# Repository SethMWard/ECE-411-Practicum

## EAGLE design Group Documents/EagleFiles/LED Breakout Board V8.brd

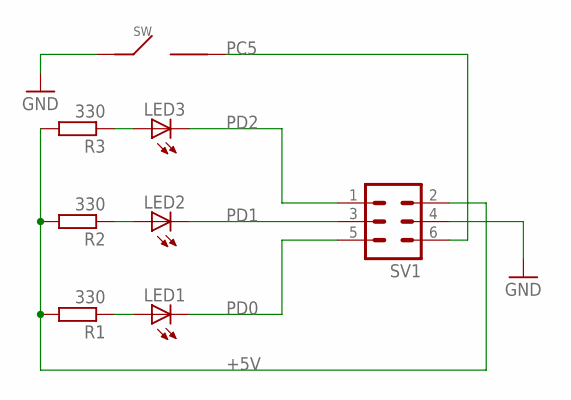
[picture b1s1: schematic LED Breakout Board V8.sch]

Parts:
LED1, LED2, LED3: LED10MM
R1, R2, R3: 330; 0207/10
SV1: MA03-2
SW: PUSHBUTTON

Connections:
+5V: R1.2, R2.2, R3.2, SV1.2
GND: SV1.4, SW.IN
unnamed: LED3.A, R3.1
unnamed: LED2.A, R2.1
unnamed: LED1.A, R1.1
PC5: SV1.6, SW.OUT
PD0: LED1.K (C), SV1.5
PD1: LED2.K (C), SV1.3
PD2: LED3.K (C), SV1.1

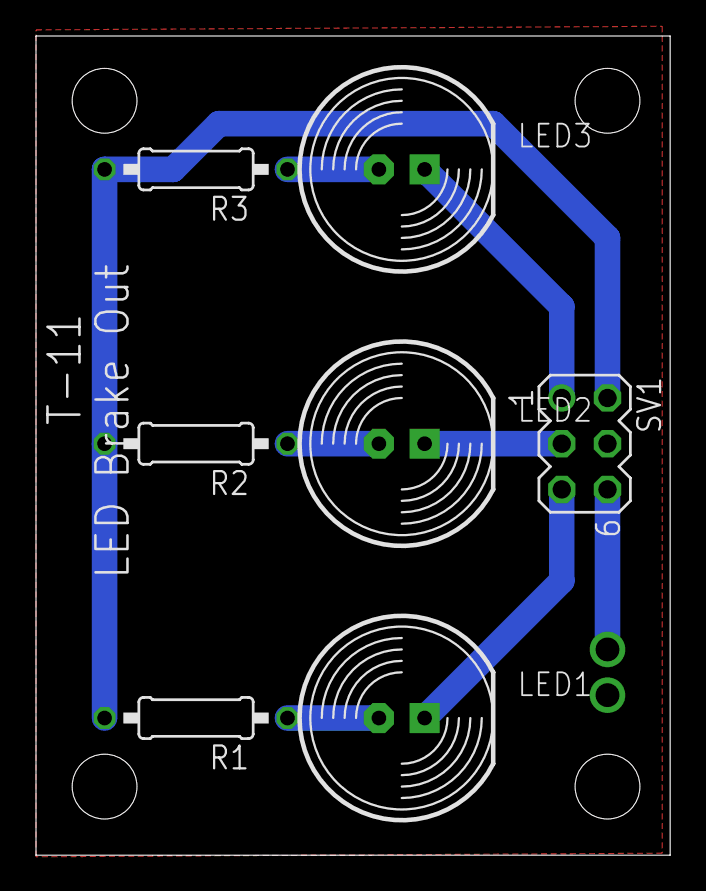
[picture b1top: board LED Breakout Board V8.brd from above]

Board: 2 copper layers, 35.2 x 45.5 mm, 8 parts (0 on the bottom side), 9 nets.

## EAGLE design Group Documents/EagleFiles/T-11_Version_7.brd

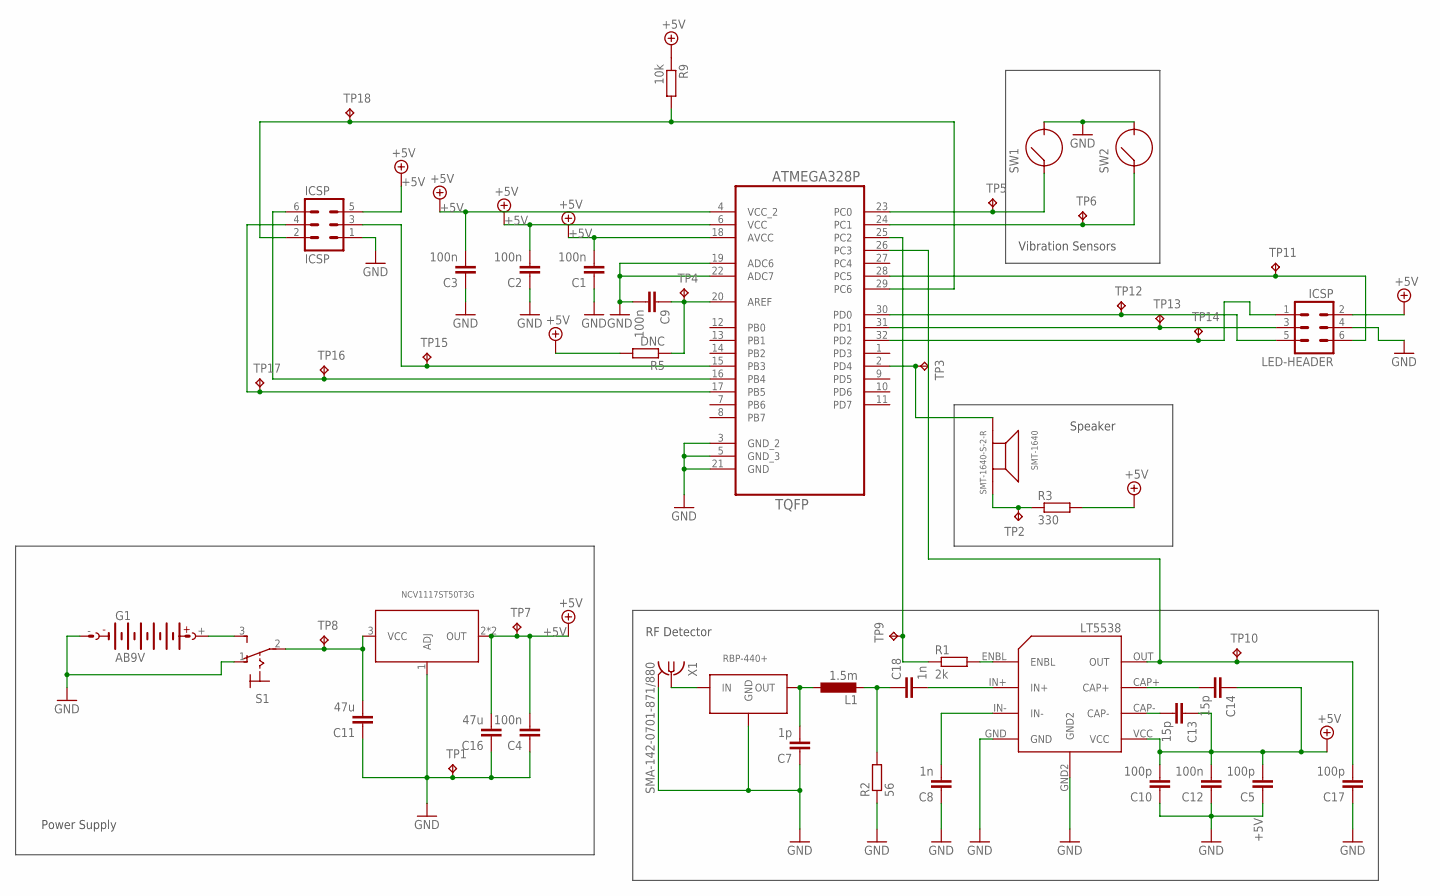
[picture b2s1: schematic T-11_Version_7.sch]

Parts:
C1, C2, C3, C4, C9, C12: 100n; C0805
C5, C10, C17: 100p; C0805
C7: 1p; C0805
C8, C18: 1n; C0805
C11, C16: 47u; C0805
C13, C14: 15p; C0805
G1: AB9V
ICSP: ICSP; MA03-2
L1: 1.5m; L2825P
LED-HEADER: ICSP; MA03-2
LT5538: LT5538
NVC1: NCV1117ST50T3G; SOT223
R1: 2k; R0805
R2: 56; R0805
R3: 330; R0805
R5: DNC; R0805
R9: 10k; R0805
RBP-440+: RBP-440+; GP731
S1: 320-916
SMT-1640: SMT-1640-S-2-R; SMT-1640
SW1, SW2: SW-1801X
TP1, TP2, TP3, TP4, TP5, TP6, TP7, TP8, TP9, TP10, TP11, TP12, TP13, TP14, TP15, TP16, TP17, TP18: TPTP10R; TP10R
U1: ATMEGA328P-AU; QFP80P900X900X120-32N
X1: SMA-142-0701-871/880; SMA-142-0701-871

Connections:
+5V: C1.2, C2.2, C3.2, C4.2, C5.2, C10.2, C12.2, C13.1, C14.1, C16.2, ICSP.5, LED-HEADER.2, LT5538.VCC, NVC1.2 (OUT), NVC1.4 (OUT), R3.2, R5.2, R9.1, TP7.TP, U1.4 (VCC_2), U1.6 (VCC), U1.18 (AVCC)
ANT_IN_1: C7.2, L1.1, RBP-440+.6 (OUT)
ANT_IN_2: C18.1, L1.2, R2.2
GND: C1.1, C2.1, C3.1, C4.1, C5.1, C7.1, C8.1, C9.2, C10.1, C11.1, C12.1, C16.1, C17.1, G1.-, ICSP.1, LED-HEADER.4, LT5538.GND, LT5538.GND2, NVC1.1 (ADJ), R2.1, RBP-440+.1 (GND), RBP-440+.3 (GND), RBP-440+.4 (GND), RBP-440+.5 (GND), RBP-440+.7 (GND), RBP-440+.8 (GND), S1.1 (O), SW1.P$2, SW2.P$2, TP1.TP, U1.3 (GND_2), U1.5 (GND_3), U1.19 (ADC6), U1.21 (GND), U1.22 (ADC7), X1.2@1 (2), X1.2@2 (2), X1.2@3 (2), X1.2@4 (2)
INDICATOR_1: LED-HEADER.1, TP14.TP, U1.32 (PD2)
INDICATOR_2: LED-HEADER.3, TP13.TP, U1.31 (PD1)
INDICATOR_3: LED-HEADER.5, TP12.TP, U1.30 (PD0)
MISO: ICSP.6, TP16.TP, U1.16 (PB4)
MOSI: ICSP.3, TP15.TP, U1.15 (PB3)
unnamed: LED-HEADER.6, TP11.TP, U1.28 (PC5)
unnamed: RBP-440+.2 (IN), X1.1
unnamed: R3.1, SMT-1640.P$1 (OUT), TP2.TP
unnamed: G1.+, S1.3 (S)
unnamed: C18.2, LT5538.IN+
unnamed: LT5538.ENBL, R1.2
unnamed: C14.2, LT5538.CAP+
unnamed: C13.2, LT5538.CAP-
unnamed: C9.1, R5.1, TP4.TP, U1.20 (AREF)
unnamed: SMT-1640.P$2 (IN), TP3.TP, U1.2 (PD4)
PS_VIN: C11.2, NVC1.3 (VCC), S1.2, TP8.TP
RESET: ICSP.2, R9.2, TP18.TP, U1.29 (PC6)
RF_ENABLE: R1.1, TP9.TP, U1.25 (PC2)
RF_IN-: C8.2, LT5538.IN-
RF_OUT: C17.2, LT5538.OUT, TP10.TP, U1.26 (PC3)
SCK: ICSP.4, TP17.TP, U1.17 (PB5)
VIB_1: SW2.P$1, TP6.TP, U1.24 (PC1)
VIB_2: SW1.P$1, TP5.TP, U1.23 (PC0)

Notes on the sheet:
Power Supply
RF Detector
Speaker
Vibration Sensors

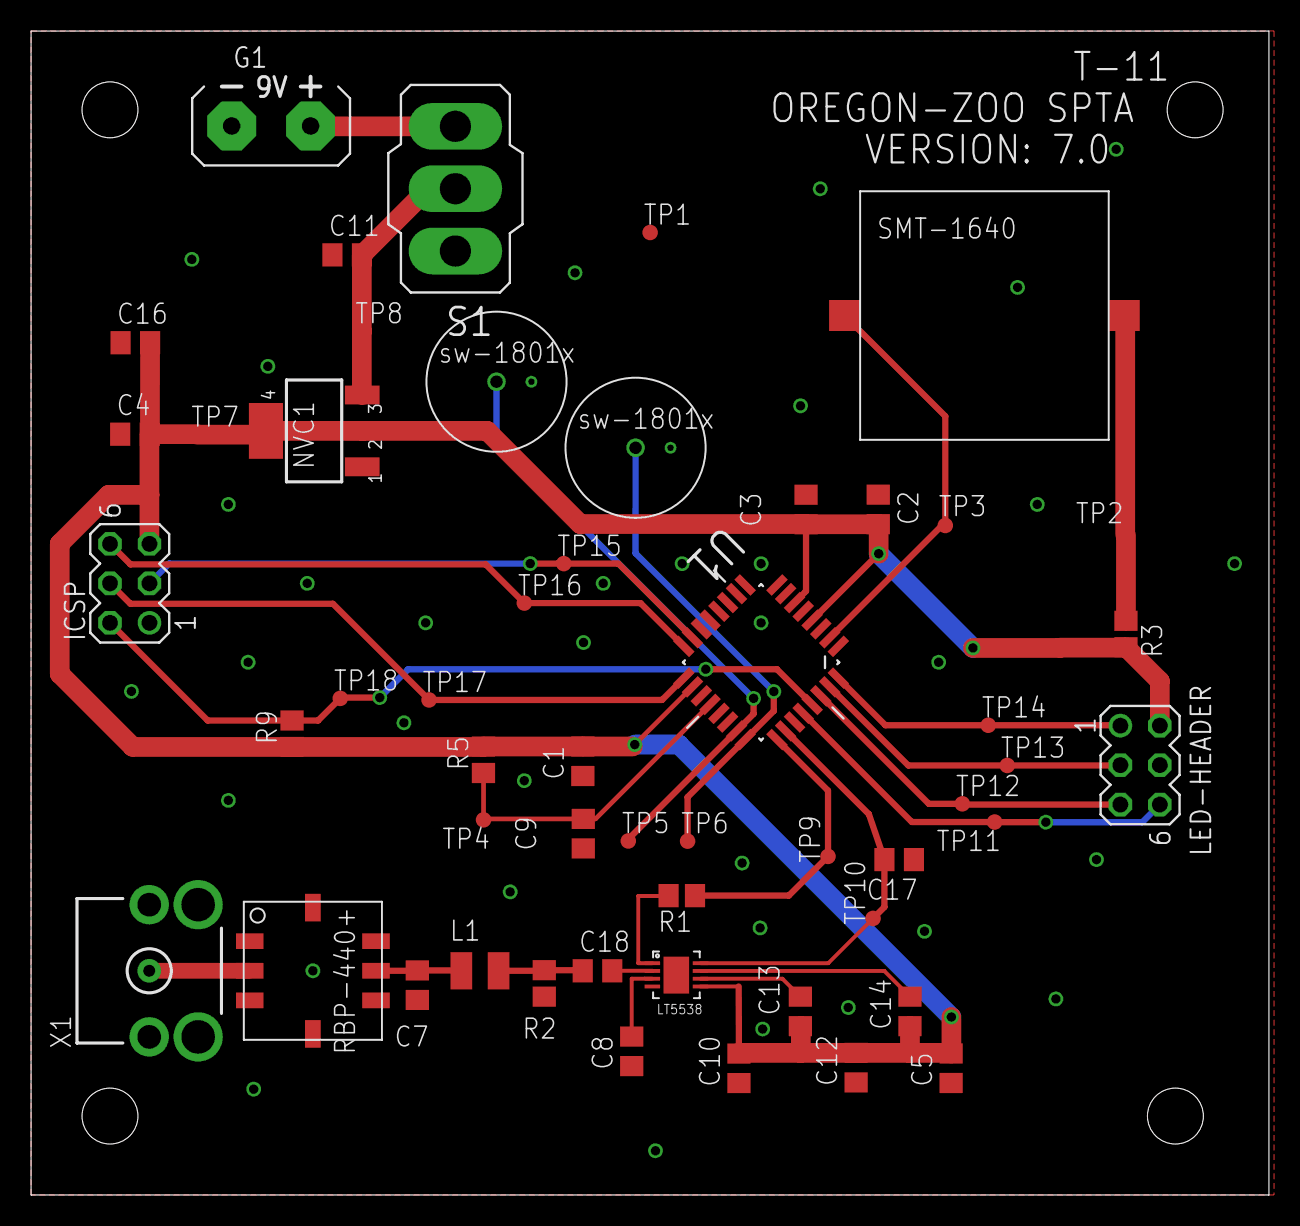
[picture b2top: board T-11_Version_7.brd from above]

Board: 2 copper layers, 79.7 x 74.9 mm, 52 parts (0 on the bottom side), 27 nets.

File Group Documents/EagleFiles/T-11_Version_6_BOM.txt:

Partlist exported from C:/Users/Devin.Lorenzen/Documents/eagle/Zoo Simulator/T-11_Version_6.sch at 11/8/2014 12:53:26 PM

Qty Value                Device               Package               Parts                                                                                             Description                                           
1                        320-916              320-916               S1                                                                                                TOGGLE SWITCH                                         
1   1.5m                 L-EUL2825P           L2825P                L1                                                                                                INDUCTOR, European symbol                             
6   100n                 C-EUC0805            C0805                 C1, C2, C3, C4, C9, C12                                                                           CAPACITOR, European symbol                            
3   100p                 C-EUC0805            C0805                 C5, C10, C17                                                                                      CAPACITOR, European symbol                            
1   10k                  R-EU_R0805           R0805                 R9                                                                                                RESISTOR, European symbol                             
2   15p                  C-EUC0805            C0805                 C13, C14                                                                                          CAPACITOR, European symbol                            
2   1n                   C-EUC0805            C0805                 C8, C18                                                                                           CAPACITOR, European symbol                            
1   1p                   C-EUC0805            C0805                 C7                                                                                                CAPACITOR, European symbol                            
1   20k                  R-EU_R0805           R0805                 R5                                                                                                RESISTOR, European symbol                             
1   2k                   R-EU_R0805           R0805                 R1                                                                                                RESISTOR, European symbol                             
1   330                  R-EU_R0805           R0805                 R3                                                                                                RESISTOR, European symbol                             
2   47u                  C-EUC0805            C0805                 C11, C16                                                                                          CAPACITOR, European symbol                            
1   56                   R-EU_R0805           R0805                 R2                                                                                                RESISTOR, European symbol                             
1   AB9V                 AB9V                 AB9V                  G1                                                                                                9-V BATTERY CLIP                                      
1   ATMEGA328P-AU        ATMEGA328P-AU        QFP80P900X900X120-32N U1                                                                                                                                                      
2   ICSP                 MA03-2               MA03-2                ICSP, LED-HEADER                                                                                  PIN HEADER                                            
1   LT5538               LT5538               LT5538                LT5538                                                                                                                                                  
1   NCV1117ST50T3G       NCV1117ST50T3G       SOT223                NVC1                                                                                                                                                    
1   RBP-440+             RBP-440+             GP731                 RBP-440+                                                                                          Band Pass Filter                                      
1   SMA-142-0701-871/880 SMA-142-0701-871/880 SMA-142-0701-871      X1                                                                                                SMA 50 Ohm End Launch Jack Receptacle - Round Contact 
1   SMT-1640-S-2-R       SMT-1640-S-2-R       SMT-1640              SMT-1640                                                                                          pizo buzzer                                           
2   SW-1801X             SW-1801X             SW-1801X              SW1, SW2                                                                                          Vibration Sensor                                      
18  TPTP10R              TPTP10R              TP10R                 TP1, TP2, TP3, TP4, TP5, TP6, TP7, TP8, TP9, TP10, TP11, TP12, TP13, TP14, TP15, TP16, TP17, TP18 Test pad

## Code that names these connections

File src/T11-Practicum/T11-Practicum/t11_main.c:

/*
 * t11_main.c
 *
 * T11 - Suspicious Package Training Device
 * Edward Sayers, Seth Ward, Devin Lorenzen, Jeremiah Franke
 * 
 */ 

/*
 * Pin Definitions
 * PC0 - Vibration Sensor 1 - PCINT8
 * PC1 - Vibration Sensor 2 - PCINT9
 * PC5 - Activation Switch  - PCINT13
 * PD0 - LED 1
 * PD1 - LED 2
 * PD2 - LED 3
 * PD4 - Buzzer
 * PC2 - RF Detector Enable
 * PC3 - RF Detector Output	- ADC3
 */

#include "t11_main.h"
#include <avr/io.h>
#include <avr/interrupt.h>
#include <util/delay.h>
#include <stdint.h>

//#define THRESHOLD 425
#define THRESHOLD 300
//#define SILENT

volatile uint16_t level;

int main(void)
{
	
	int i; // Counter index
	
	/* Set pin directions and initial values */
	clearbit(DDRC, PINC0);		// Vibration Sensor 1 as input
	clearbit(DDRC, PINC1);		// Vibration Sensor 2 as input
	clearbit(DDRC, PINC5);		// Activation Switch as input
	setbit(PORTC, PINC0);		// Enable pull-up for Vibration Sensor 1
	setbit(PORTC, PINC1);		// Enable pull-up for Vibration Sensor 2
	setbit(PORTD, PIND0);		// Turn LED 1 off
	setbit(PORTD, PIND1);		// Turn LED 2 off
	setbit(PORTD, PIND2);		// Turn LED 3 off
	setbit(DDRD, PIND0);		// LED 1 as output
	setbit(DDRD, PIND1);		// LED 2 as output
	setbit(DDRD, PIND2);		// LED 3 as output
	setbit(DDRD, PIND4);		// Buzzer as output
	setbit(DDRC, PINC2);		// RF Detector Enable as output
	setbit(PORTC, PINC2);		// Enable RF Detector
	

	
	/* Setup ADC */
	
	/* Prescaler determines the clock rate of the ADC, 50 - 200 kHz is recommended.
	 *
	 * Clock speed is 1MHz so a prescaler of 64 provides an appropriate frequency
	 * Setting ADPS2...0 to 110 sets the prescaler to 64 
	 */
	setbit(ADCSRA, ADPS2);
	setbit(ADCSRA, ADPS1);
	clearbit(ADCSRA, ADPS0);
	
	clearbit(ADMUX, ADLAR);		// Right align ADC register
	
	/* Select ADC3 by setting MUX3...0 to 0011 in ADMUX */
	clearbit(ADMUX, MUX3);
	clearbit(ADMUX, MUX2);
	setbit(ADMUX, MUX1);
	setbit(ADMUX, MUX0);
	
	/* Select external voltage reference by setting REFS1...0 to 00 in ADMUX */
	clearbit(ADMUX, REFS1);
	setbit(ADMUX, REFS0);
	
	setbit(ADCSRA, ADIE);		// Enable ADC interrupts
	setbit(ADCSRA, ADEN);		// Enable ADC
	
	/* Toggle Activation LED with half second delay
	 * Delay allows time for device to be placed
	 */
	for (i = 0; i < 15; ++i)
	{
		_delay_ms(500);
		togglebit(PORTD, PIND0);
	}
	/* Setup Interrupts */
	setbit(PCICR, PCIE1);		// Enable interrupts from PCINT[14:8]
	setbit(PCMSK1, PCINT8);		// Enable interrupt from vibration sensor 1
	setbit(PCMSK1, PCINT9);		// Enable interrupt from vibration sensor 2
	sei();						// Enable interrupts
	setbit(ADCSRA, ADSC);		// Start conversion
	
	/* Loop while waiting for interrupts */
    while(1)
    {
		// wait for interrupt
    }
}

/* Interrupt handler for ADC interrupts */
ISR(ADC_vect)
{
	uint8_t low_bits = ADCL;					// Get lower 8 bits
	level = (ADCH << 8) | low_bits;	// Add upper 2 bits to lower 8 bits
	
	if (level > THRESHOLD)
	{
		triggerDevice(0);
	}
	else
	{
		setbit(ADCSRA, ADSC); // Start another conversion
	}
	
		
}

/* Interrupt handler for PCINT1 interrupts */
ISR(PCINT1_vect)
{
	triggerDevice(1);
}

/* Triggers device
 * 0 = RF
 * 1 = Movement
 */
void triggerDevice(char source)
{
	cli();
	switch (source)
	{
	case 0:
		clearbit(PORTD, PIND2); // Turn on RF LED
		break;
	case 1:
	default:
		clearbit(PORTD, PIND1); // Turn on Movement LED
		break;		
	}
	soundBuzzer();	
}

// Turns buzzer on
void soundBuzzer(void)
{
#ifndef SILENT
		while (1)
		{
			togglebit(PORTD, PIND4);
			_delay_us(100);
		}
#endif
}

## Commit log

2014-10-13 Add Draft of decision matrix
    Draft of decision matrix
2014-10-13 Format Update
    Changed formatting to be more presentable.
2014-10-13 Spelling Fixes
2014-10-13 Moved
    Moved into new directory
2014-10-13 Updated Preferences
2014-10-13 Actually updated rankings
2014-10-13 Added Project Proposal
2014-10-23 Revert "Update README.md"
    This reverts commit 2465d79c01e6b5d9cc2f25d53a6e33412a0bbadb.
2014-10-23 CAD Libraries
    Added CAD Libraries For sw-180xx, atmega, 328p-AU, LT5538
2014-10-24 Update
    Added ATMEGA8U2-MU, Package; TQFP32 to AVA.lbr
2014-10-24 LT5538 test board v1
    Added a test board for the LT5538
2014-10-26 Design Requirements
    Added Design Requirements
2014-10-27 T-11 Schematic. V1.00
    Added Eagle schematic.
2014-10-27 Project Design Specifications updated
    I updated the motion sensor portion of the document and changed some of
    the autocorrect silliness that finds its way into the documents. Had to
    change the extension because I do not have word on my home computer.
2014-10-27 Edward's WSR
2014-10-27 Create Week3Edward
2014-10-27 Rename Week3Edward to Week3Edward.md
2014-10-27 Revised pds
2014-10-27 Create Lorenzen-week#3
    added WPR
2014-10-27 Rename Lorenzen-week#3 to Lorenzen-week#3.md
2014-10-29 Week3Seth.md
2014-10-29 Added test code
    Preliminary code
2014-10-29 Rename T-11_Version.1.00.sch to T-11_Version_1_00.sch
2014-10-29 Rename T-11_Version_1_00.sch to T-11_Version.1.00.sch
    Not sure why I initially changed the name
2014-10-30 Updated schematic to 1.1
    Added ICSP header
    Resolved ERC problems
    Removed crystal
    Changed power switch and added 9V clip
2014-11-01 Added data sheets for parts
2014-11-01 Added data sheets for buzzer
2014-11-01 Schematic Version 1.2
2014-11-04 Submitted week four status report
2014-11-04 Added bandpass filter datasheet
2014-11-04 Update
    Updated and added library files.
    Updated schematic.
2014-11-05 Added eagle files and LED breakout board
2014-11-05 Osh Park Design Rules
2014-11-05 T-11 SCH&BRD
    Updated schematic
    Added PCB layout.
2014-11-05 LED Brake out BRD V2
    Changed LED PKG
    Changed header pins outs
    Added GPIO pin labels to nets
    Added PCB BRD
2014-11-05 SCH&BRD files
    Updated schematic
    Added PCB layout bdr file
    Added part name to LT5538
2014-11-05 WPR_Week#4
    Added weekly progress report.
2014-11-05 SCH@BRD files
    added a GND via under the ATMEGA382-AU
2014-11-05 SCH&BDR Update
    updated schematic and board to version 5 (view Read_Me)
2014-11-05 LED Brakeout Update
    sch
    Added frame to sch file.
    brd
    Added product name to brd file.
    Increased board size.
    Added 3.6mm mounting holes.
2014-11-05 Updated schematic to resolve ERC issues
    Updated package to resolve wrong pin type
    Added values to C13 and C14
    Resolved overlapping pins
    Moved overlapping test points
2014-11-07 LT5534 Library
    Created library for LT5534
2014-11-08 BOM
    Added BOM
2014-11-08 T-11 SPTA_V6-update
    Updated Read_me
    updated schematic
    updated board layout
    Updated BOM
2014-11-08 LED-Brake-out-V4
    moved mounting holes
    changed resistor PKG size.
    added BOM
2014-11-09 Added board and schematic image files
2014-11-09 Added schematic image files Rev 6
2014-11-09 Added project schedule draft
2014-11-10 Updated the Project Schedule
    Finished out the project schedule, needs reviewing.
2014-11-10 MOAR
    More changes, this time with Flair!
2014-11-10 Updated Hours
    Should be final draft.
2014-11-10 layout 7
    updated schematic.
    updated SPTA layout.
    updated LED brake-out layout.
2014-11-10 Added Systems Design and Modeling
    Added the System Design and Modeling section. This is what was missing
    from this week.
2014-11-10 Trying to fix git issue
2014-11-10 And trying the commit again
    here
2014-11-10 Create Week5Edward
2014-11-10 Rename Week5Edward to Week5Edward.md
2014-11-12 Update Lorenzen-Week#5.md
    Fixed formatting Issue
2014-11-16 Added UML State Machine
2014-11-17 Block Diagram
    created block diagram and descriptions
2014-11-17 UML Activity View
2014-11-17 Updated Homework 5
2014-11-17 Weekly Status Report
    Updated week 5 and week 6
2014-11-20 Updating the Project Schedule
    Newest Project Schedule
2014-11-22 Create Week5Jeremiah
2014-11-22 Create Week6Jeremiah
2014-11-23 Added Test Plan TOC
2014-11-24 Test Plan
    Uploaded test plan skeleton
2014-11-24 Updated Test Plan
    Section 1 is open to review
2014-11-24 Test Plan rev 3
2014-11-24 Test Cases
2014-11-24 User test SP
2014-11-24 spta name change
2014-11-24 Updated section 5
2014-11-24 HW 6
    Updated the group test plan
2014-11-30 Consolidated Documents
2014-11-30 LED V7
    Changed LED to 10mm
    Removed R2, R3.
    Moved traces to bottom layer
2014-11-30 LED V7
    changed 330 ohm PKG
    changed switch to ground
2014-12-04 Added Projcet Code
2014-12-06 WeeklyReport
2014-12-06 All code functionality working
2014-12-07 SPTA Case
2014-12-10 Updated some testing documents
    I will be changing these again when we meet, I think we should integrate
    the CPU into the unit testing.
2014-12-11 Create Week9Seth
2014-12-11 Rename Week9Seth to Week9Seth,md
2014-12-12 LED BOB
2014-12-12 images creation
2014-12-12 Update HW 5
2014-12-12 SPTA BOM
2014-12-12 Added Presentation
2014-12-12 Added Schematic Image
2014-12-12 Presintation
2014-12-15 Updated code
